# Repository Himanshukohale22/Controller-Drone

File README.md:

# SKY
CONTROLLER FOR DRONE

stm32F411xc on board controller flight controller.

Specification:
On board chip of controller is STM32F4XC high performance microcontroller.
Board contains gyroscope and accelorometer for flight controlling and PID motion.

Hardware design:
STM32F411xc main controller.
mpu6050 gyroscope and accelorometer sensor.
bmp280 pressure and altitude sensor.
nrf24 RF module for on board communicaton between base station and flight ROCEKT.

scematics img:

pcb img:

3D:

datasheet:

stm32f411 

https://www.st.com/resource/en/datasheet/stm32f411re.pdf

MPU6050

https://invensense.tdk.com/wp-content/uploads/2015/02/MPU-6000-Datasheet1.pdf

BMP280

https://cdn-shop.adafruit.com/datasheets/BST-BMP280-DS001-11.pdf

NRF24

https://www.sparkfun.com/datasheets/Components/SMD/nRF24L01Pluss_Preliminary_Product_Specification_v1_0.pdf

BUILTIN MICRO SD CARD

https://components101.com/modules/micro-sd-card-module-pinout-features-datasheet-alternatives

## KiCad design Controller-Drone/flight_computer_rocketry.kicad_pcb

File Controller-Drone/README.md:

# FLIGHT COMPUTER
controller for any four motors based flying object according to specification mentioned below.

This repository contains hardware files and gerber files of board . this is open source project board can be used aacording to features mentioned below.

### BOARD SPECIFICATION.
---

* STM32f4 cortex M4 based on board microcontroller for precision and fligt data simulation.
  * core -  Arm® 32-bit Cortex®-M4 CPU with FPU, Adaptive real-time accelerator .
  *  1 Mbyte of Flash memory
  *  192+4 Kbytes of SRAM
  *  Serial wire debug
* sensors
  * MPU9250.(IMU)
    *  9-axis of freedom. (6 are used).
    * accerelometer an gyroscopic values
    * Higher calibration precision.
    * for statbility and orientation of board/vehicle.
    * configured with SPI1.
  * BMP280 .(Barometer)
    * configured with I2C .
    * barometer for altitude calculations . helps to hover the flight.
    * absolutely accurate p = 950 -- 1100 hPa.
  * NRF module
    * nrf module for communication upto 1km.
    * configured with SPI2.
* for programme the ,board include four pins ckl , io , pwr , gnd as in 1.27mm pins(SWD). use ST-LINK.
* power input
  * usbB mini for testing testing.
  * jst connector i/p from 12v to 27v .

### schematics   
---

## 3D 
---

## Tools 

* [kicad](https://www.kicad.org/)

* [STM32cubeide](https://www.st.com/en/development-tools/stm32cubeide.html)

## Reference 
---

[stm32f411](https://www.st.com/resource/en/datasheet/stm32f411re.pdf)

[MPU6050](https://invensense.tdk.com/wp-content/uploads/2015/02/MPU-6000-Datasheet1.pdf)

[BMP280](https://cdn-shop.adafruit.com/datasheets/BST-BMP280-DS001-11.pdf)

[NRF24](https://www.sparkfun.com/datasheets/Components/SMD/nRF24L01Pluss_Preliminary_Product_Specification_v1_0.pdf)

## future work 
---
* work with higher level cortex controller.(ex f7/f8)
* include SD card for collecting flight data.
* include FVP cameras. and configuring. collecting photos/videos.
* higher level nrf modules for rf communications.

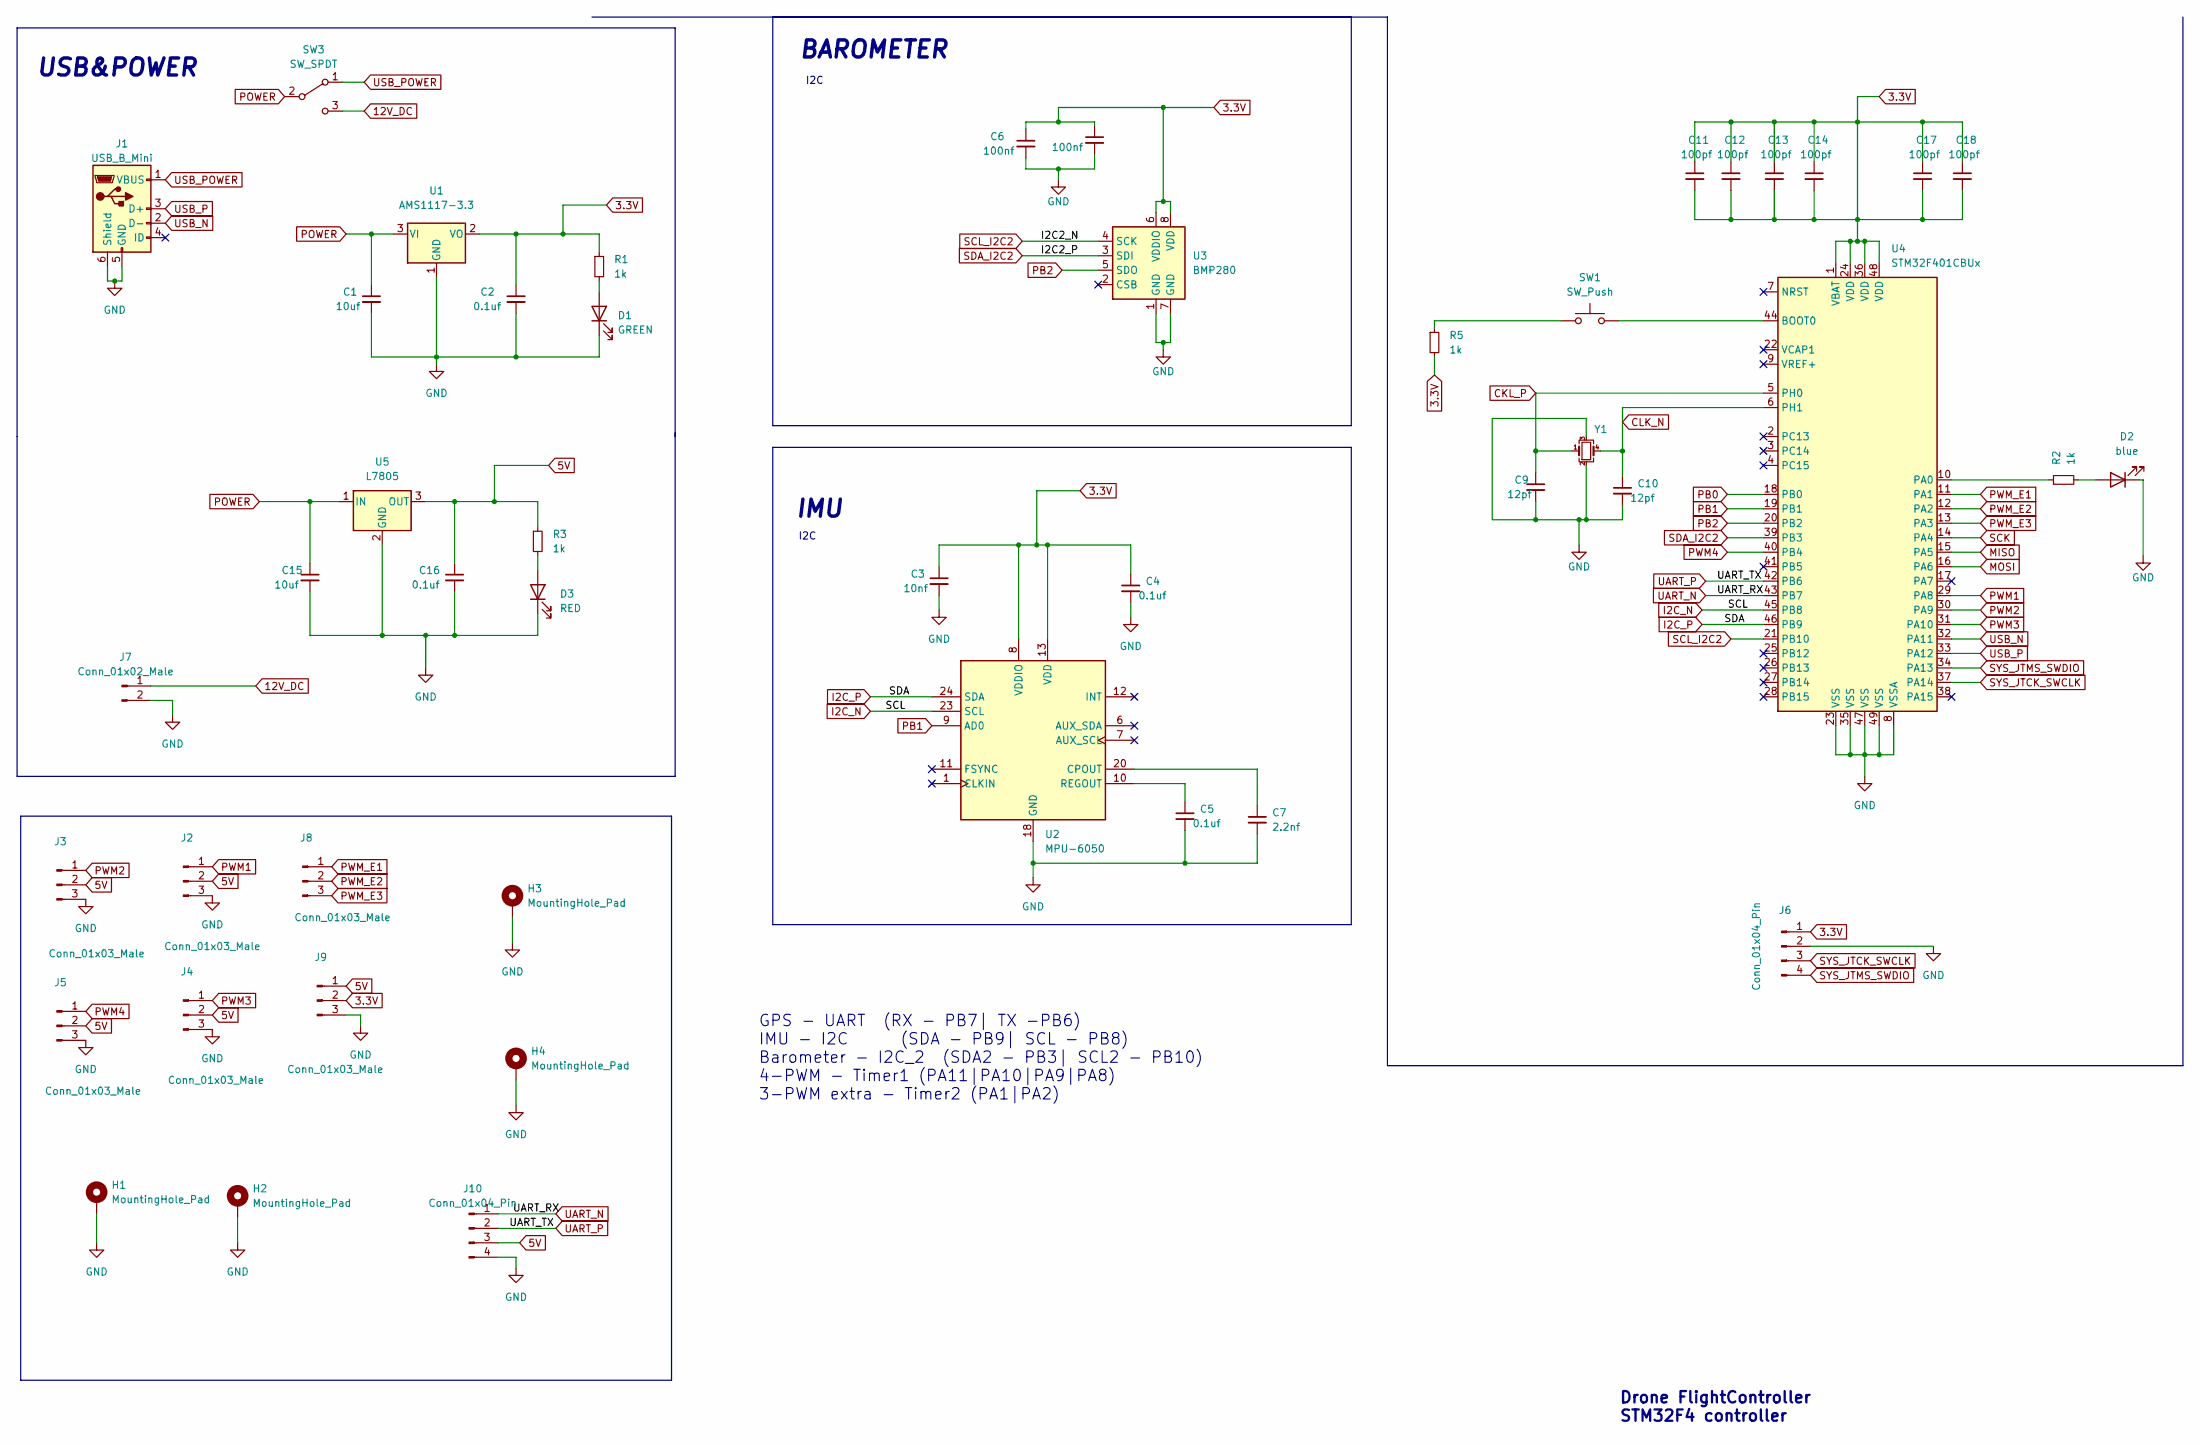
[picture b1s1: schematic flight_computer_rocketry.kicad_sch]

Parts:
C1, C15: 10uf; C_0603_1608Metric_Pad1.08x0.95mm_HandSolder
C2, C4, C5, C16: 0.1uf; C_0603_1608Metric_Pad1.08x0.95mm_HandSolder
C3: 10nf; C_0603_1608Metric_Pad1.08x0.95mm_HandSolder
C6, C8: 100nf; C_0603_1608Metric_Pad1.08x0.95mm_HandSolder
C7: 2.2nf; C_0603_1608Metric_Pad1.08x0.95mm_HandSolder
C9, C10: 12pf; C_0603_1608Metric_Pad1.08x0.95mm_HandSolder
C11, C12, C13, C14, C17, C18: 100pf; C_0603_1608Metric_Pad1.08x0.95mm_HandSolder
D1: GREEN; LED_0603_1608Metric_Pad1.05x0.95mm_HandSolder
D2: blue; LED_0603_1608Metric_Pad1.05x0.95mm_HandSolder
D3: RED; LED_0603_1608Metric_Pad1.05x0.95mm_HandSolder
H1, H2, H3, H4: MountingHole_Pad; MountingHole_2.2mm_M2_Pad_Via
J1: USB_B_Mini; USB_Micro-B_Molex_47346-0001
J2, J3, J4, J5, J8: Conn_01x03_Male; JST_EH_S3B-EH_1x03_P2.50mm_Horizontal
J6: Conn_01x04_Pin; JST_GH_BM04B-GHS-TBT_1x04-1MP_P1.25mm_Vertical
J7: Conn_01x02_Male; JST_EH_S2B-EH_1x02_P2.50mm_Horizontal
J9: Conn_01x03_Male; JST_EH_B3B-EH-A_1x03_P2.50mm_Vertical
J10: Conn_01x04_Pin; JST_GH_SM04B-GHS-TB_1x04-1MP_P1.25mm_Horizontal
R1, R2, R3, R5: 1k; R_0805_2012Metric_Pad1.20x1.40mm_HandSolder
SW1: SW_Push; SW_SPST_TL3342
SW3: SW_SPDT; SW_CuK_OS102011MA1QN1_SPDT_Angled
U1: AMS1117-3.3; SOT-223-3_TabPin2
U2: MPU-6050; InvenSense_QFN-24_4x4mm_P0.5mm
U3: BMP280; Bosch_LGA-8_2x2.5mm_P0.65mm_ClockwisePinNumbering
U4: STM32F401CBUx; QFN-48-1EP_7x7mm_P0.5mm_EP5.6x5.6mm
U5: L7805; SOT-223-3_TabPin2
Y1: Crystal_GND23_Small; Crystal_SMD_0603-4Pin_6.0x3.5mm

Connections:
3.3V: C2.1, C3.1, C4.1, C6.1, C8.1, C11.1, C11.2, C12.1, C12.2, C13.1, C13.2, C14.1, C14.2, C17.1, C17.2, C18.1, C18.2, J6.1, J9.2, R1.1, R5.2, U1.2 (VO), U2.8 (VDDIO), U2.13 (VDD), U3.6 (VDDIO), U3.8 (VDD), U4.1 (VBAT), U4.24 (VDD), U4.36 (VDD), U4.48 (VDD)
5V: C16.1, J2.2, J3.2, J4.2, J5.2, J9.1, J10.3, R3.1, U5.3 (OUT)
12V_DC: J7.1, SW3.3 (C)
CKL_P: C9.1, U4.5 (PH0), Y1.1
CLK_N: C10.1, U4.6 (PH1), Y1.4
GND: C1.2, C2.2, C3.2, C4.2, C5.2, C6.2, C7.2, C8.2, C9.2, C10.2, C15.2, C16.2, D1.1 (K), D2.1 (K), D3.1 (K), H1.1, H2.1, H3.1, H4.1, J1.5 (GND), J1.6 (Shield), J2.3, J3.3, J4.3, J5.3, J6.2, J7.2, J9.3, J10.4, U1.1 (GND), U2.18 (GND), U3.1 (GND), U3.7 (GND), U4.8 (VSSA), U4.23 (VSS), U4.35 (VSS), U4.47 (VSS), U4.49 (VSS), U5.2 (GND), Y1.2, Y1.3
I2C_N: U2.23 (SCL), U4.45 (PB8)
I2C_P: U2.24 (SDA), U4.46 (PB9)
MISO: U4.15 (PA5)
MOSI: U4.16 (PA6)
unnamed: D1.2 (A), R1.2
unnamed: D2.2 (A), R2.2
unnamed: D3.2 (A), R3.2
unnamed: R5.1, SW1.1
unnamed: C7.1, U2.20 (CPOUT)
unnamed: C5.1, U2.10 (REGOUT)
unnamed: SW1.2, U4.44 (BOOT0)
unnamed: R2.1, U4.10 (PA0)
PB0: U4.18 (PB0)
PB1: U2.9 (AD0), U4.19 (PB1)
PB2: U3.5 (SDO), U4.20 (PB2)
POWER: C1.1, C15.1, SW3.2 (B), U1.3 (VI), U5.1 (IN)
PWM1: J2.1, U4.29 (PA8)
PWM2: J3.1, U4.30 (PA9)
PWM3: J4.1, U4.31 (PA10)
PWM4: J5.1, U4.40 (PB4)
PWM_E1: J8.1, U4.11 (PA1)
PWM_E2: J8.2, U4.12 (PA2)
PWM_E3: J8.3, U4.13 (PA3)
SCK: U4.14 (PA4)
SCL_I2C2: U3.4 (SCK), U4.21 (PB10)
SDA_I2C2: U3.3 (SDI), U4.39 (PB3)
SYS_JTCK_SWCLK: J6.3, U4.37 (PA14)
SYS_JTMS_SWDIO: J6.4, U4.34 (PA13)
UART_N: J10.1, U4.43 (PB7)
UART_P: J10.2, U4.42 (PB6)
USB_N: J1.2 (D-), U4.32 (PA11)
USB_P: J1.3 (D+), U4.33 (PA12)
USB_POWER: J1.1 (VBUS), SW3.1 (A)

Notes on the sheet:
I2C
GPS - UART (RX - PB7| TX -PB6) IMU - I2C (SDA - PB9| SCL - PB8) Barometer - I2C_2 (SDA2 - PB3| SCL2 - PB10) 4-PWM - Timer1 (PA11|PA10|PA9|PA8) 3-PWM extra - Timer2 (PA1|PA2)
IMU
Drone FlightController STM32F4 controller
USB&POWER
BAROMETER

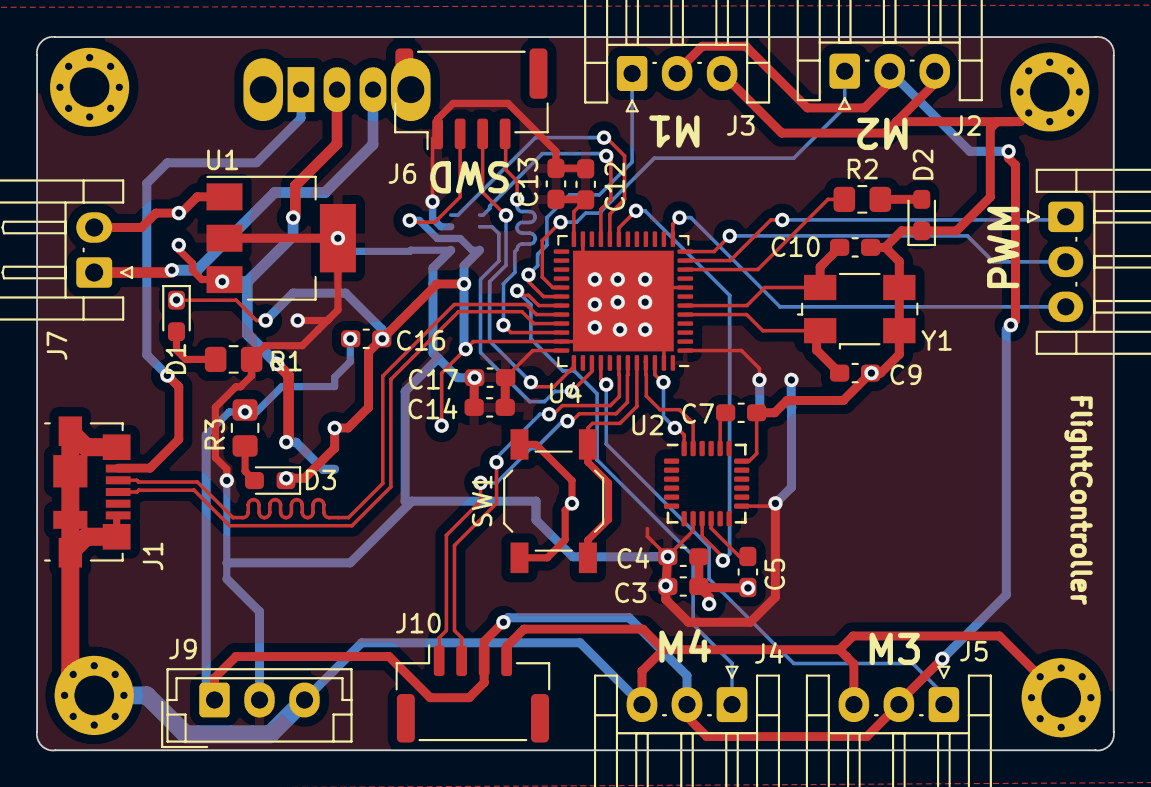
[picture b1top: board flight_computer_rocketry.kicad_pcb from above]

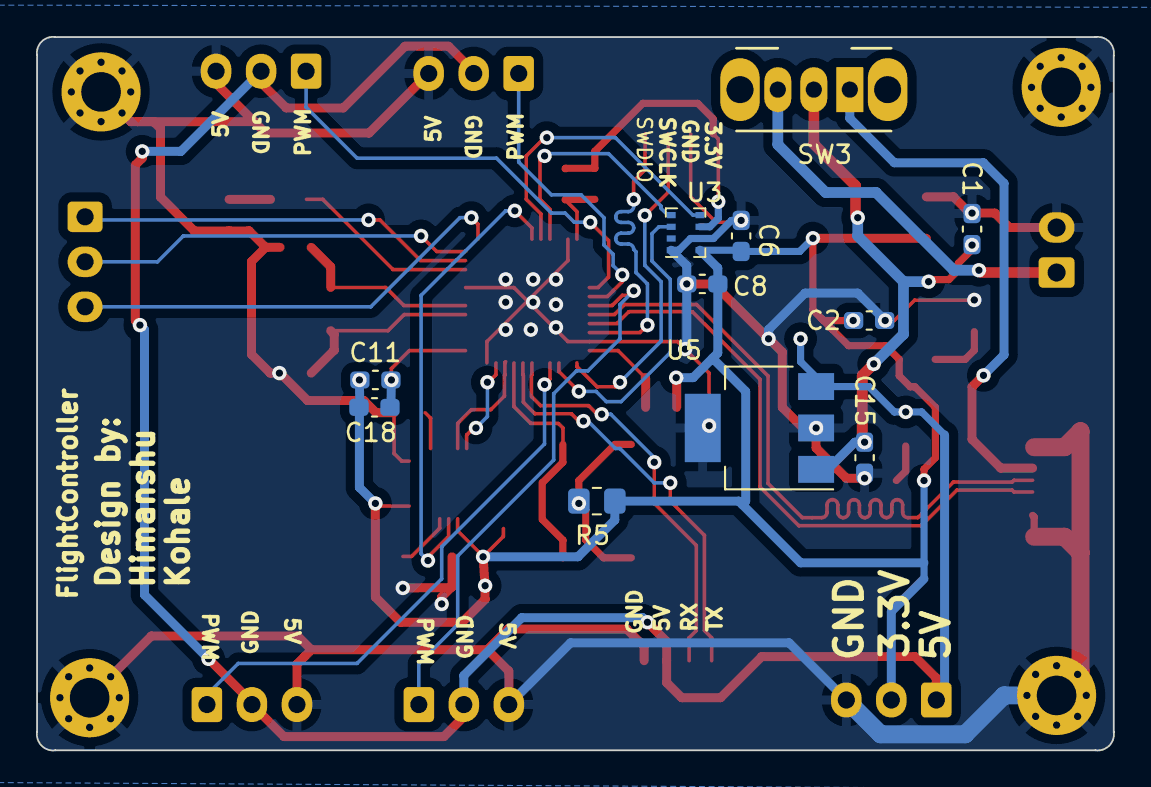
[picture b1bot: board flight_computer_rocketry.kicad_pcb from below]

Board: 2 copper layers, 59.8 x 39.6 mm, 47 parts (11 on the bottom side), 35 nets.

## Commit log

2023-07-04 added
2023-07-04 schematics added
2023-07-04 images
2023-07-04 images added
2025-06-07 adding tar file
2025-06-07 adding hardware files and images
